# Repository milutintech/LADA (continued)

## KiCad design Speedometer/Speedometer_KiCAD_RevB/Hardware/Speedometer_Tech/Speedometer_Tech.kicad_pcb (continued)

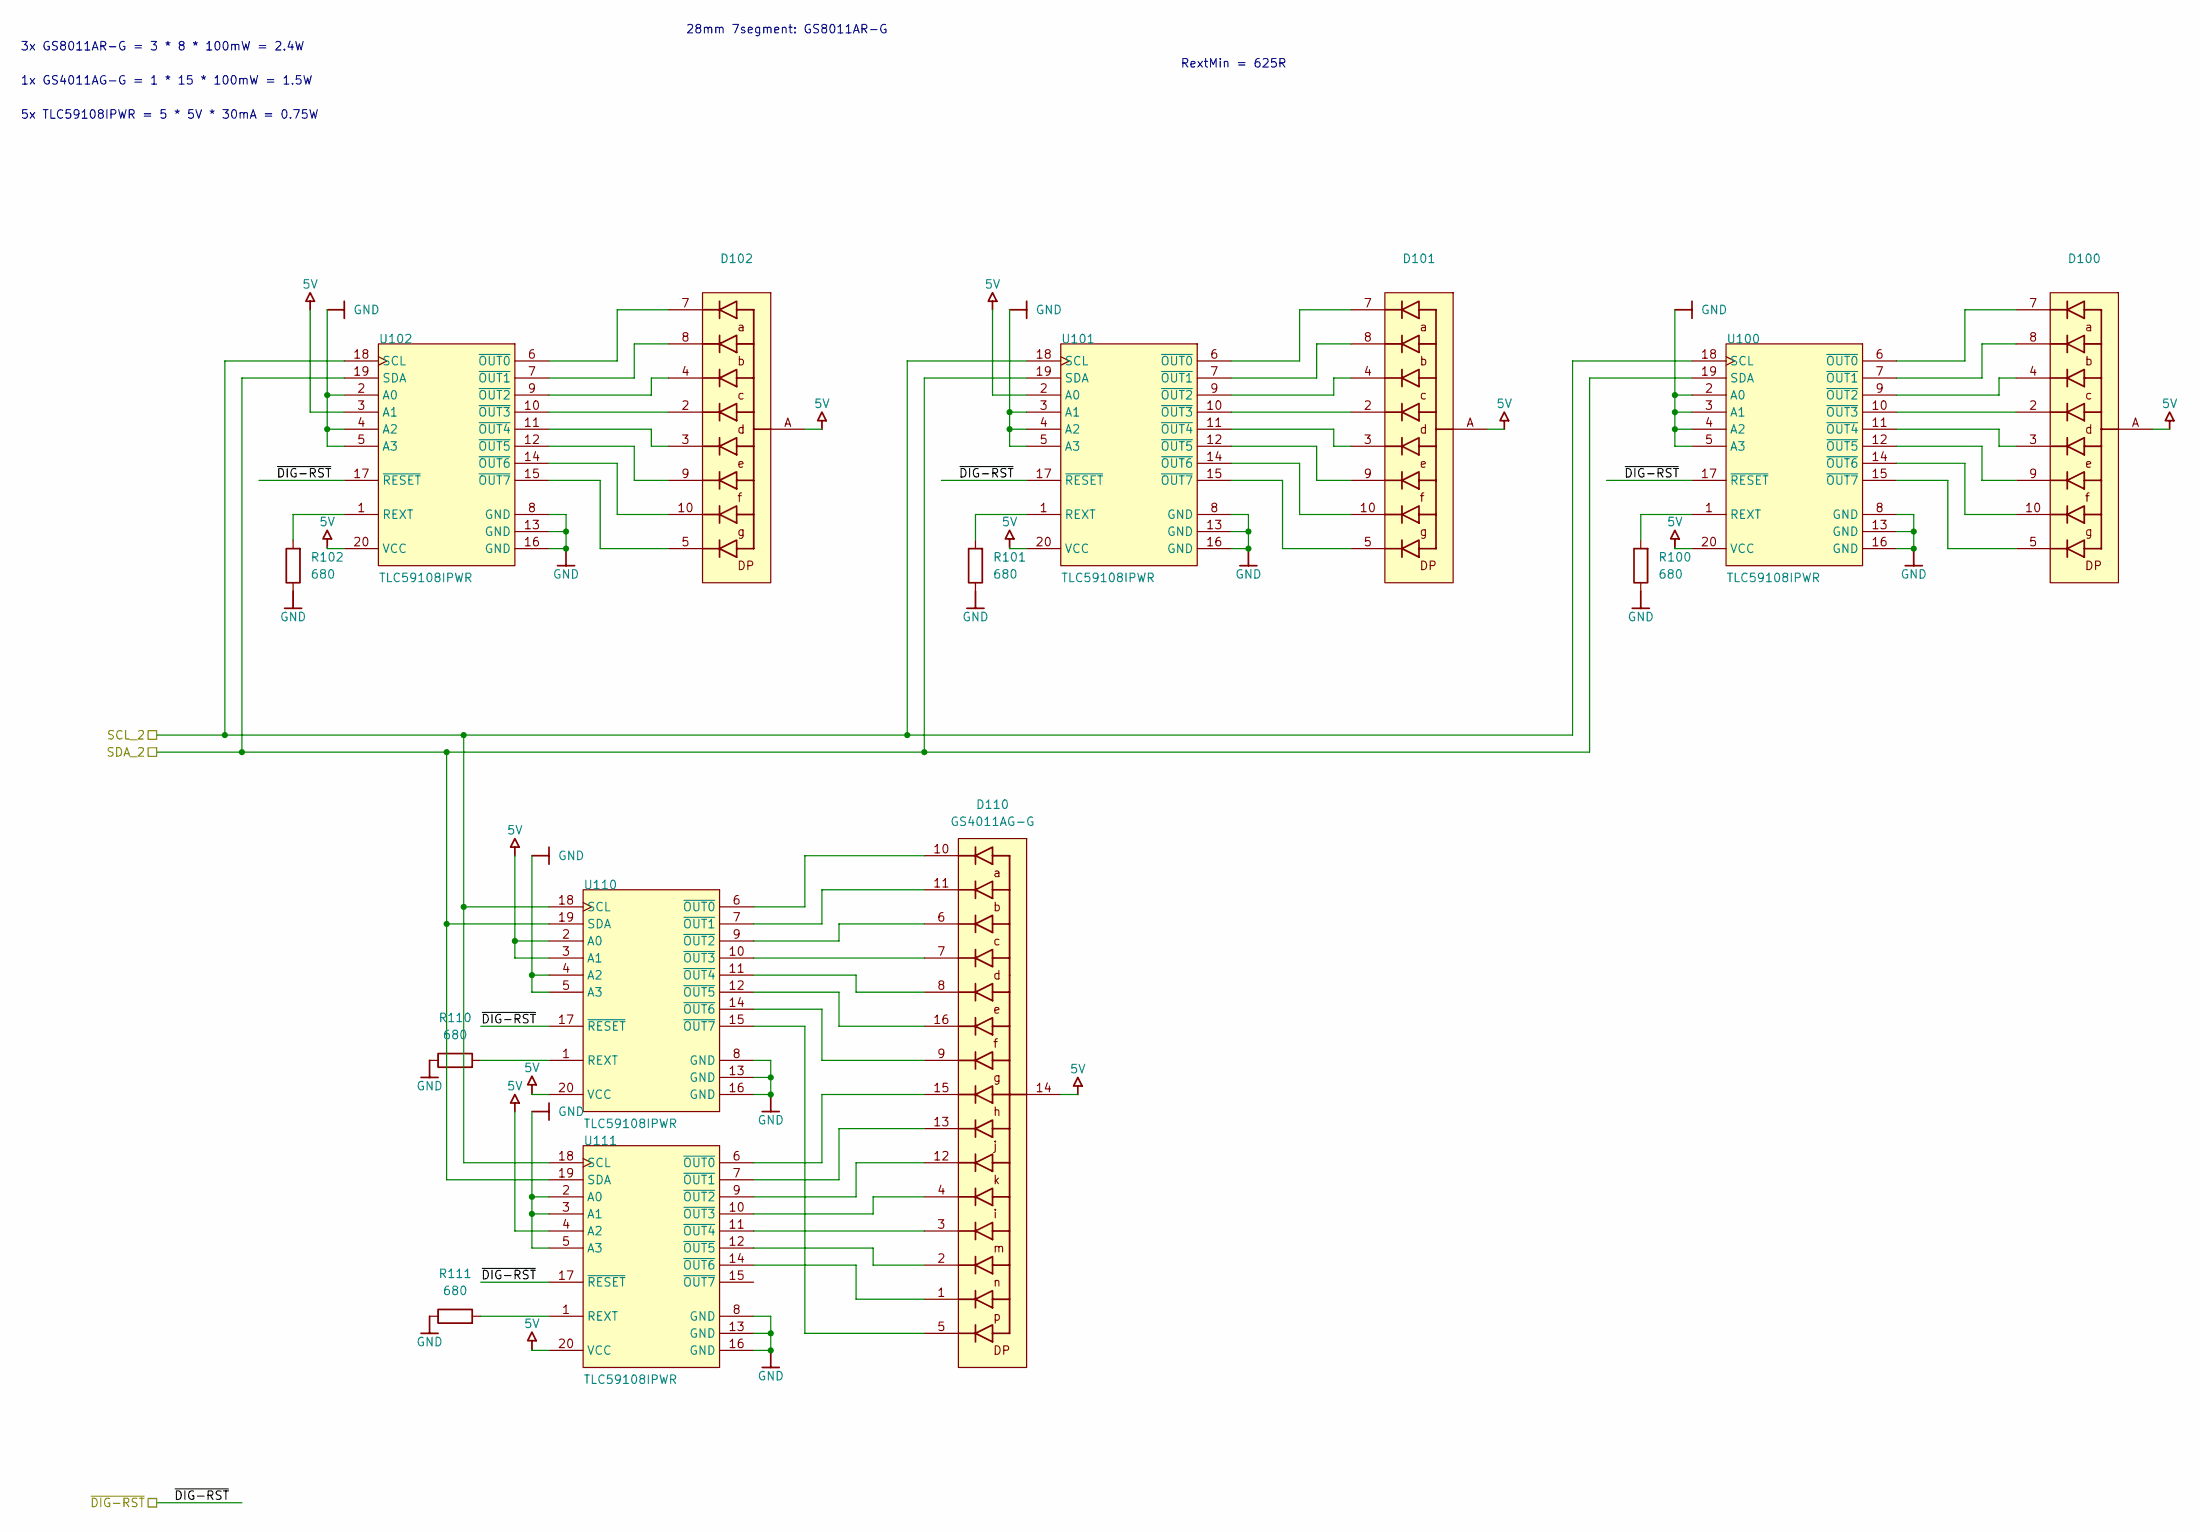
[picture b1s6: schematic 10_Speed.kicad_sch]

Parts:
D100, D101, D102: GS8011AR-G
D110: GS4011AG-G
R100, R101, R102, R110, R111: 680; R_0603_1608Metric
U100, U101, U102, U110, U111: TLC59108IPWR; TSSOP-20_4.4x6.5mm_P0.65mm; PARTNUMBER TLC59108IPWR

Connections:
5V: D100.A, D101.A, D102.A, D110.14, U100.20 (VCC), U101.2 (A0), U101.20 (VCC), U102.3 (A1), U102.20 (VCC), U110.2 (A0), U110.3 (A1), U110.20 (VCC), U111.4 (A2), U111.20 (VCC); also elsewhere on the board
/Distance/~DIG-RST: U100.17 (~RESET), U101.17 (~RESET), U102.17 (~RESET), U110.17 (~RESET), U111.17 (~RESET); also elsewhere on the board
/Speed/SCL_2: U100.18 (SCL), U101.18 (SCL), U102.18 (SCL), U110.18 (SCL), U111.18 (SCL); also elsewhere on the board
/Speed/SDA_2: U100.19 (SDA), U101.19 (SDA), U102.19 (SDA), U110.19 (SDA), U111.19 (SDA); also elsewhere on the board
GND: R100.1, R101.1, R102.1, R110.1, R111.1, U100.2 (A0), U100.3 (A1), U100.4 (A2), U100.5 (A3), U100.8 (GND), U100.13 (GND), U100.16 (GND), U101.3 (A1), U101.4 (A2), U101.5 (A3), U101.8 (GND), U101.13 (GND), U101.16 (GND), U102.2 (A0), U102.4 (A2), U102.5 (A3), U102.8 (GND), U102.13 (GND), U102.16 (GND), U110.4 (A2), U110.5 (A3), U110.8 (GND), U110.13 (GND), U110.16 (GND), U111.2 (A0), U111.3 (A1), U111.5 (A3), U111.8 (GND), U111.13 (GND), U111.16 (GND); also elsewhere on the board
unnamed: R100.2, U100.1 (REXT)
unnamed: D100.7, U100.6 (~OUT0)
unnamed: D100.8, U100.7 (~OUT1)
unnamed: D100.4, U100.9 (~OUT2)
unnamed: D100.2, U100.10 (~OUT3)
unnamed: D100.3, U100.11 (~OUT4)
unnamed: D100.9, U100.12 (~OUT5)
unnamed: D100.10, U100.14 (~OUT6)
unnamed: D100.5, U100.15 (~OUT7)
unnamed: R101.2, U101.1 (REXT)
unnamed: D101.7, U101.6 (~OUT0)
unnamed: D101.8, U101.7 (~OUT1)
unnamed: D101.4, U101.9 (~OUT2)
unnamed: D101.2, U101.10 (~OUT3)
unnamed: D101.3, U101.11 (~OUT4)
unnamed: D101.9, U101.12 (~OUT5)
unnamed: D101.10, U101.14 (~OUT6)
unnamed: D101.5, U101.15 (~OUT7)
unnamed: R102.2, U102.1 (REXT)
unnamed: D102.7, U102.6 (~OUT0)
unnamed: D102.8, U102.7 (~OUT1)
unnamed: D102.4, U102.9 (~OUT2)
unnamed: D102.2, U102.10 (~OUT3)
unnamed: D102.3, U102.11 (~OUT4)
unnamed: D102.9, U102.12 (~OUT5)
unnamed: D102.10, U102.14 (~OUT6)
unnamed: D102.5, U102.15 (~OUT7)
unnamed: R110.2, U110.1 (REXT)
unnamed: D110.10, U110.6 (~OUT0)
unnamed: D110.11, U110.7 (~OUT1)
unnamed: D110.6, U110.9 (~OUT2)
unnamed: D110.7, U110.10 (~OUT3)
unnamed: D110.8, U110.11 (~OUT4)
unnamed: D110.16, U110.12 (~OUT5)
unnamed: D110.9, U110.14 (~OUT6)
unnamed: D110.5, U110.15 (~OUT7)
unnamed: R111.2, U111.1 (REXT)
unnamed: D110.15, U111.6 (~OUT0)
unnamed: D110.13, U111.7 (~OUT1)
unnamed: D110.12, U111.9 (~OUT2)
unnamed: D110.4, U111.10 (~OUT3)
unnamed: D110.3, U111.11 (~OUT4)
unnamed: D110.2, U111.12 (~OUT5)
unnamed: D110.1, U111.14 (~OUT6)

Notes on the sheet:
28mm 7segment: GS8011AR-G
RextMin = 625R
5x TLC59108IPWR = 5 * 5V * 30mA = 0.75W
3x GS8011AR-G = 3 * 8 * 100mW = 2.4W
1x GS4011AG-G = 1 * 15 * 100mW = 1.5W

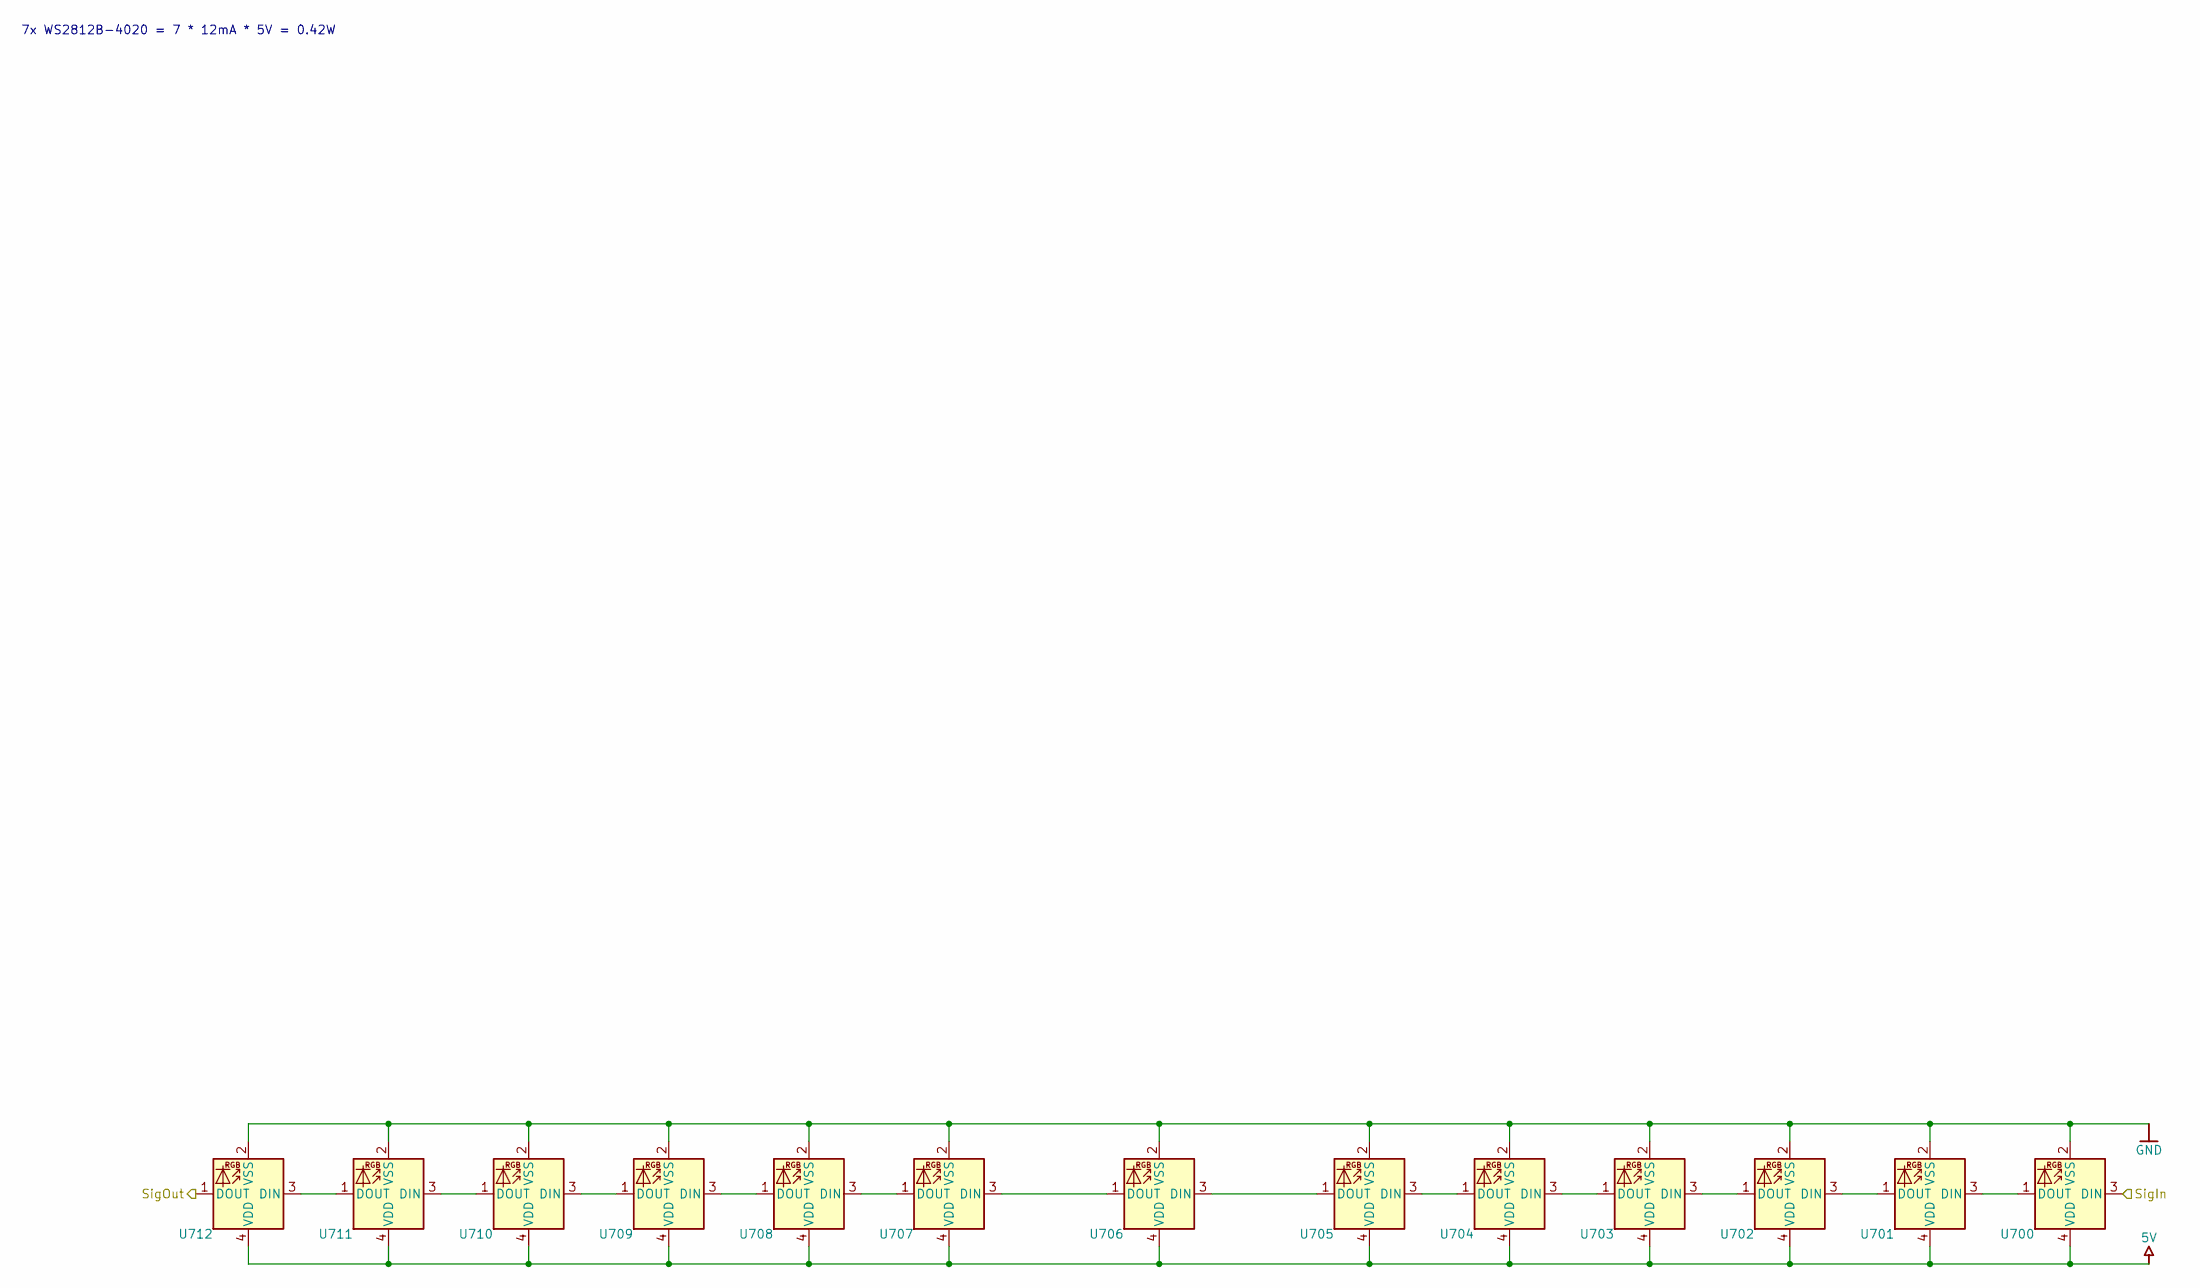
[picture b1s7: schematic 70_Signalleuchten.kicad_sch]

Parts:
U700, U701, U702, U703, U704, U705, U706, U707, U708, U709, U710, U711, U712: WS2812B-4020_2; LED_WS2812B-2020_PLCC4_2.0x2.0mm

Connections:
5V: U700.4 (VDD), U701.4 (VDD), U702.4 (VDD), U703.4 (VDD), U704.4 (VDD), U705.4 (VDD), U706.4 (VDD), U707.4 (VDD), U708.4 (VDD), U709.4 (VDD), U710.4 (VDD), U711.4 (VDD), U712.4 (VDD); also elsewhere on the board
/SOC/SocOut: U700.3 (DIN); also elsewhere on the board
/States/SigOut: U712.1 (DOUT); also elsewhere on the board
GND: U700.2 (VSS), U701.2 (VSS), U702.2 (VSS), U703.2 (VSS), U704.2 (VSS), U705.2 (VSS), U706.2 (VSS), U707.2 (VSS), U708.2 (VSS), U709.2 (VSS), U710.2 (VSS), U711.2 (VSS), U712.2 (VSS); also elsewhere on the board
unnamed: U700.1 (DOUT), U701.3 (DIN)
unnamed: U701.1 (DOUT), U702.3 (DIN)
unnamed: U702.1 (DOUT), U703.3 (DIN)
unnamed: U703.1 (DOUT), U704.3 (DIN)
unnamed: U704.1 (DOUT), U705.3 (DIN)
unnamed: U705.1 (DOUT), U706.3 (DIN)
unnamed: U706.1 (DOUT), U707.3 (DIN)
unnamed: U707.1 (DOUT), U708.3 (DIN)
unnamed: U708.1 (DOUT), U709.3 (DIN)
unnamed: U709.1 (DOUT), U710.3 (DIN)
unnamed: U710.1 (DOUT), U711.3 (DIN)
unnamed: U711.1 (DOUT), U712.3 (DIN)

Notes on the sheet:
7x WS2812B-4020 = 7 * 12mA * 5V = 0.42W

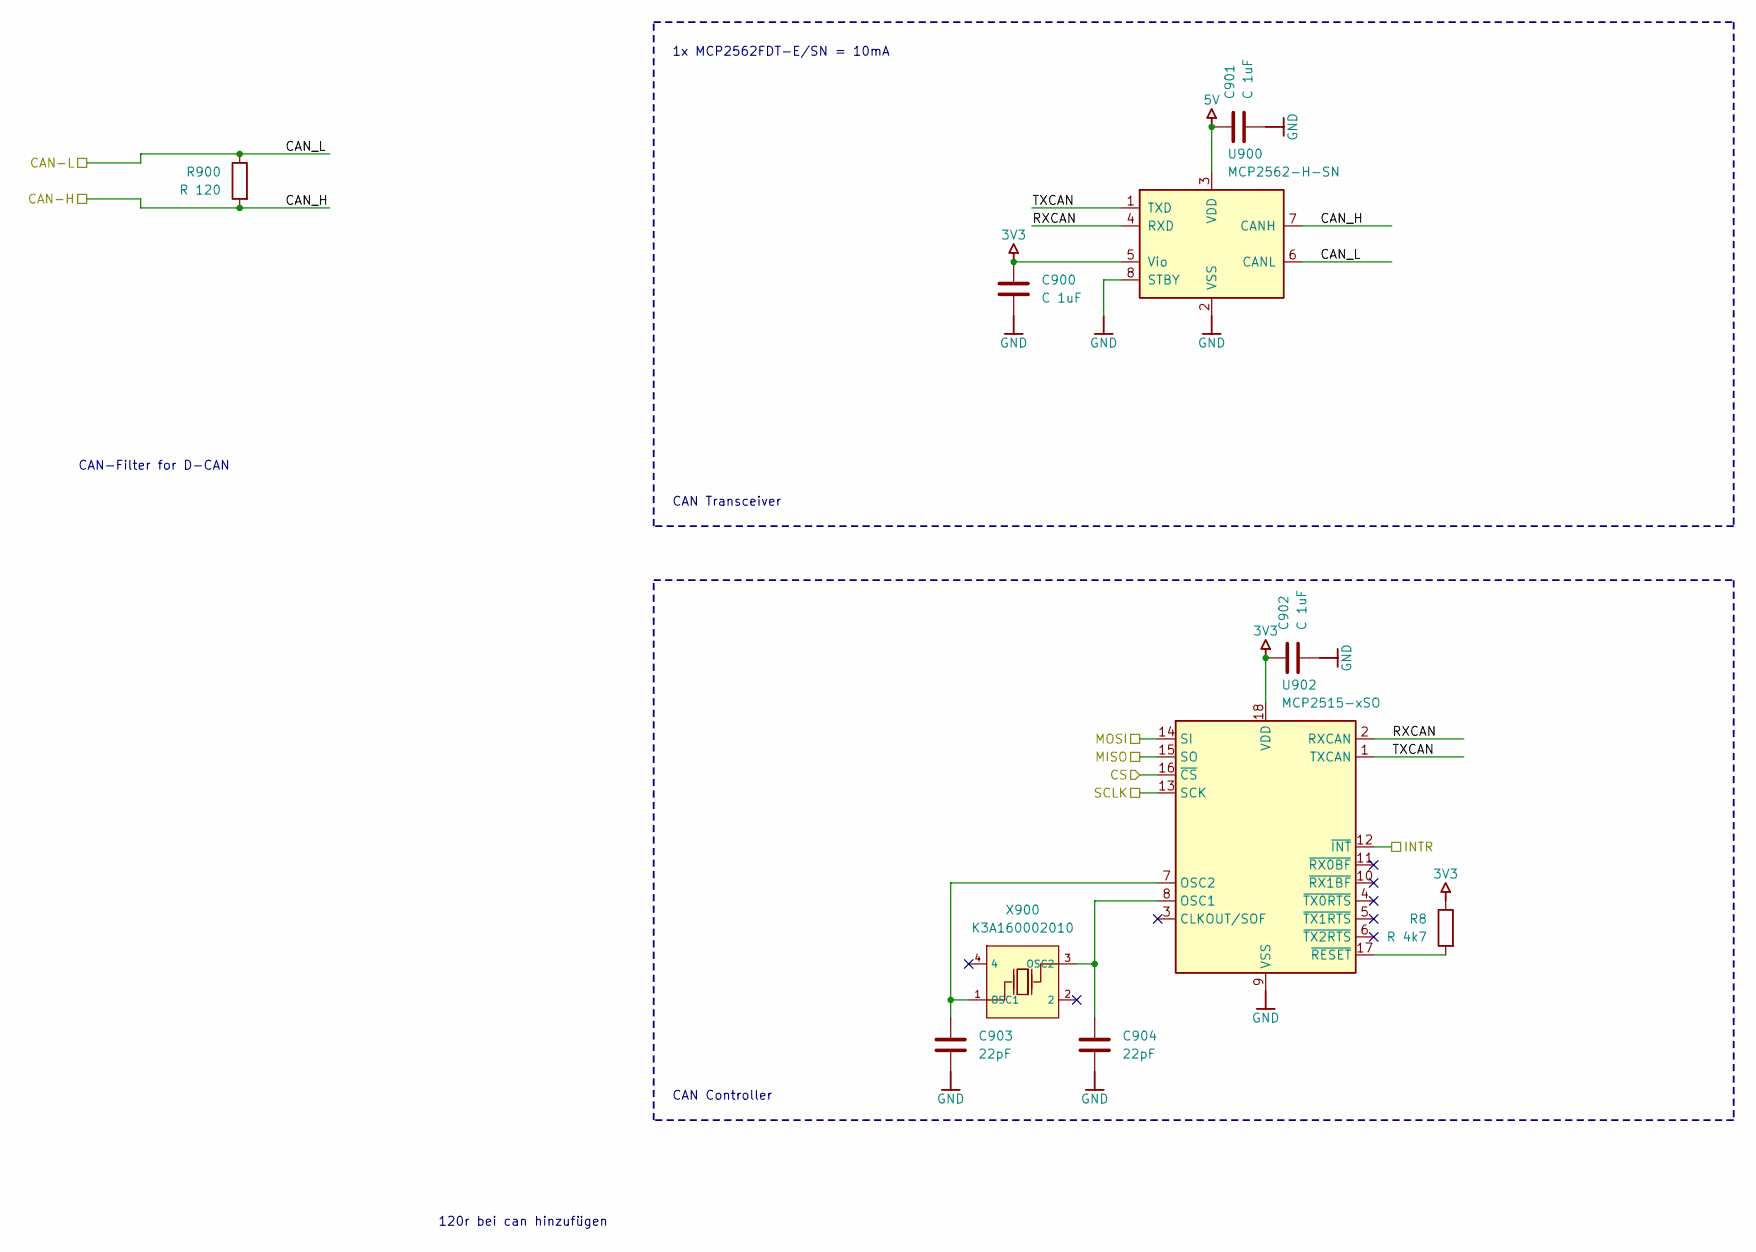
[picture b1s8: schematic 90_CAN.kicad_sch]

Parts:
C900, C901, C902: C 1uF; C_0603_1608Metric
C903, C904: 22pF; C_0603_1608Metric
R8: R 4k7; R_0603_1608Metric
R900: R 120; R_0603_1608Metric
U900: MCP2562-H-SN; SOIC-8_3.9x4.9mm_P1.27mm
U902: MCP2515-xSO; SOIC-18W_7.5x11.6mm_P1.27mm
X900: K3A160002010; Crystal_SMD_3225-4Pin_3.2x2.5mm; LCSC C368736

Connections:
3V3: C900.1, C902.1, R8.1, U900.5 (Vio), U902.18 (VDD); also elsewhere on the board
5V: C901.1, U900.3 (VDD); also elsewhere on the board
/CAN/CAN_H: R900.2, U900.7 (CANH); also elsewhere on the board
/CAN/CAN_L: R900.1, U900.6 (CANL); also elsewhere on the board
/CAN/INTR: U902.12 (~INT); also elsewhere on the board
/CAN/RXCAN: U900.4 (RXD), U902.2 (RXCAN)
/CAN/SCLK: U902.13 (SCK); also elsewhere on the board
/CAN/TXCAN: U900.1 (TXD), U902.1 (TXCAN)
/esp32s3/CS: U902.16 (~CS); also elsewhere on the board
/esp32s3/MISO: U902.15 (SO); also elsewhere on the board
/esp32s3/MOSI: U902.14 (SI); also elsewhere on the board
GND: C900.2, C901.2, C902.2, C903.2, C904.2, U900.2 (VSS), U900.8 (STBY), U902.9 (VSS); also elsewhere on the board
unnamed: C904.1, U902.8 (OSC1), X900.3 (OSC2)
unnamed: C903.1, U902.7 (OSC2), X900.1 (OSC1)
unnamed: R8.2, U902.17 (~RESET)

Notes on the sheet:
CAN-Filter for D-CAN
1x MCP2562FDT-E/SN = 10mA
120r bei can hinzufügen
CAN Transceiver
CAN Controller

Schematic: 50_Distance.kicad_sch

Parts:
D510, D511, D512, D513, D514, D515, D520, D521, D522, D523: 10mm 7-Segment; GS2011AG-G
R510, R511, R512, R513, R514, R515, R520, R521, R522, R523: 680; R_0603_1608Metric
U510, U511, U512, U513, U514, U515, U520, U521, U522, U523: TLC59108IPWR; TSSOP-20_4.4x6.5mm_P0.65mm; PARTNUMBER TLC59108IPWR

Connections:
5V: D510.A, D511.A, D512.A, D513.A, D514.A, D515.A, D520.A, D521.A, D522.A, D523.A, U510.20 (VCC), U511.2 (A0), U511.20 (VCC), U512.3 (A1), U512.20 (VCC), U513.2 (A0), U513.3 (A1), U513.20 (VCC), U514.4 (A2), U514.20 (VCC), U515.2 (A0), U515.4 (A2), U515.20 (VCC), U520.3 (A1), U520.4 (A2), U520.20 (VCC), U521.2 (A0), U521.3 (A1), U521.4 (A2), U521.20 (VCC), U522.5 (A3), U522.20 (VCC), U523.2 (A0), U523.5 (A3), U523.20 (VCC); also elsewhere on the board
/Distance/SCL: U510.18 (SCL), U511.18 (SCL), U512.18 (SCL), U513.18 (SCL), U514.18 (SCL), U515.18 (SCL), U520.18 (SCL), U521.18 (SCL), U522.18 (SCL), U523.18 (SCL); also elsewhere on the board
/Distance/SDA: U510.19 (SDA), U511.19 (SDA), U512.19 (SDA), U513.19 (SDA), U514.19 (SDA), U515.19 (SDA), U520.19 (SDA), U521.19 (SDA), U522.19 (SDA), U523.19 (SDA); also elsewhere on the board
/Distance/~DIG-RST: U510.17 (~RESET), U511.17 (~RESET), U512.17 (~RESET), U513.17 (~RESET), U514.17 (~RESET), U515.17 (~RESET), U520.17 (~RESET), U521.17 (~RESET), U522.17 (~RESET), U523.17 (~RESET); also elsewhere on the board
GND: R510.2, R511.2, R512.2, R513.2, R514.2, R515.2, R520.2, R521.2, R522.2, R523.2, U510.2 (A0), U510.3 (A1), U510.4 (A2), U510.5 (A3), U510.8 (GND), U510.13 (GND), U510.16 (GND), U511.3 (A1), U511.4 (A2), U511.5 (A3), U511.8 (GND), U511.13 (GND), U511.16 (GND), U512.2 (A0), U512.4 (A2), U512.5 (A3), U512.8 (GND), U512.13 (GND), U512.16 (GND), U513.4 (A2), U513.5 (A3), U513.8 (GND), U513.13 (GND), U513.16 (GND), U514.2 (A0), U514.3 (A1), U514.5 (A3), U514.8 (GND), U514.13 (GND), U514.16 (GND), U515.3 (A1), U515.5 (A3), U515.8 (GND), U515.13 (GND), U515.16 (GND), U520.2 (A0), U520.5 (A3), U520.8 (GND), U520.13 (GND), U520.16 (GND), U521.5 (A3), U521.8 (GND), U521.13 (GND), U521.16 (GND), U522.2 (A0), U522.3 (A1), U522.4 (A2), U522.8 (GND), U522.13 (GND), U522.16 (GND), U523.3 (A1), U523.4 (A2), U523.8 (GND), U523.13 (GND), U523.16 (GND); also elsewhere on the board
unnamed: R510.1, U510.1 (REXT)
unnamed: D510.7, U510.6 (~OUT0)
unnamed: D510.6, U510.7 (~OUT1)
unnamed: D510.4, U510.9 (~OUT2)
unnamed: D510.2, U510.10 (~OUT3)
unnamed: D510.1, U510.11 (~OUT4)
unnamed: D510.9, U510.12 (~OUT5)
unnamed: D510.10, U510.14 (~OUT6)
unnamed: D510.5, U510.15 (~OUT7)
unnamed: R511.1, U511.1 (REXT)
unnamed: D511.7, U511.6 (~OUT0)
unnamed: D511.6, U511.7 (~OUT1)
unnamed: D511.4, U511.9 (~OUT2)
unnamed: D511.2, U511.10 (~OUT3)
unnamed: D511.1, U511.11 (~OUT4)
unnamed: D511.9, U511.12 (~OUT5)
unnamed: D511.10, U511.14 (~OUT6)
unnamed: D511.5, U511.15 (~OUT7)
unnamed: R512.1, U512.1 (REXT)
unnamed: D512.7, U512.6 (~OUT0)
unnamed: D512.6, U512.7 (~OUT1)
unnamed: D512.4, U512.9 (~OUT2)
unnamed: D512.2, U512.10 (~OUT3)
unnamed: D512.1, U512.11 (~OUT4)
unnamed: D512.9, U512.12 (~OUT5)
unnamed: D512.10, U512.14 (~OUT6)
unnamed: D512.5, U512.15 (~OUT7)
unnamed: R513.1, U513.1 (REXT)
unnamed: D513.7, U513.6 (~OUT0)
unnamed: D513.6, U513.7 (~OUT1)
unnamed: D513.4, U513.9 (~OUT2)
unnamed: D513.2, U513.10 (~OUT3)
unnamed: D513.1, U513.11 (~OUT4)
unnamed: D513.9, U513.12 (~OUT5)
unnamed: D513.10, U513.14 (~OUT6)
unnamed: D513.5, U513.15 (~OUT7)
unnamed: R514.1, U514.1 (REXT)
unnamed: D514.7, U514.6 (~OUT0)
unnamed: D514.6, U514.7 (~OUT1)
unnamed: D514.4, U514.9 (~OUT2)
unnamed: D514.2, U514.10 (~OUT3)
unnamed: D514.1, U514.11 (~OUT4)
unnamed: D514.9, U514.12 (~OUT5)
unnamed: D514.10, U514.14 (~OUT6)
unnamed: D514.5, U514.15 (~OUT7)
unnamed: R515.1, U515.1 (REXT)
unnamed: D515.7, U515.6 (~OUT0)
unnamed: D515.6, U515.7 (~OUT1)
unnamed: D515.4, U515.9 (~OUT2)
unnamed: D515.2, U515.10 (~OUT3)
unnamed: D515.1, U515.11 (~OUT4)
unnamed: D515.9, U515.12 (~OUT5)
unnamed: D515.10, U515.14 (~OUT6)
unnamed: D515.5, U515.15 (~OUT7)
unnamed: R520.1, U520.1 (REXT)
unnamed: D520.7, U520.6 (~OUT0)
unnamed: D520.6, U520.7 (~OUT1)
unnamed: D520.4, U520.9 (~OUT2)
unnamed: D520.2, U520.10 (~OUT3)
unnamed: D520.1, U520.11 (~OUT4)
unnamed: D520.9, U520.12 (~OUT5)
unnamed: D520.10, U520.14 (~OUT6)
unnamed: D520.5, U520.15 (~OUT7)
unnamed: R521.1, U521.1 (REXT)
unnamed: D521.7, U521.6 (~OUT0)
unnamed: D521.6, U521.7 (~OUT1)
unnamed: D521.4, U521.9 (~OUT2)
unnamed: D521.2, U521.10 (~OUT3)
unnamed: D521.1, U521.11 (~OUT4)
unnamed: D521.9, U521.12 (~OUT5)
unnamed: D521.10, U521.14 (~OUT6)
unnamed: D521.5, U521.15 (~OUT7)
unnamed: R522.1, U522.1 (REXT)
unnamed: D522.7, U522.6 (~OUT0)
unnamed: D522.6, U522.7 (~OUT1)
unnamed: D522.4, U522.9 (~OUT2)
unnamed: D522.2, U522.10 (~OUT3)
unnamed: D522.1, U522.11 (~OUT4)
unnamed: D522.9, U522.12 (~OUT5)
unnamed: D522.10, U522.14 (~OUT6)
unnamed: D522.5, U522.15 (~OUT7)
unnamed: R523.1, U523.1 (REXT)
unnamed: D523.7, U523.6 (~OUT0)
unnamed: D523.6, U523.7 (~OUT1)
unnamed: D523.4, U523.9 (~OUT2)
unnamed: D523.2, U523.10 (~OUT3)
unnamed: D523.1, U523.11 (~OUT4)
unnamed: D523.9, U523.12 (~OUT5)
unnamed: D523.10, U523.14 (~OUT6)
unnamed: D523.5, U523.15 (~OUT7)

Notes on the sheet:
Numbering from right to left
Trip km
10x GS2011AG-G = 10 * 8 * 100mW = 8W
Total km
10x TLC59108IPWR = 10 * 5V * 30mA = 1.5W

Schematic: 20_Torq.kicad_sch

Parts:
U205, U206, U207, U208, U209, U210, U211, U212, U213, U214, U215, U216, U217, U218, U219, U220, U221, U222, U223, U224, U225, U226, U227, U228, U229, U230, U231, U232, U233, U234, U235, U236, U237, U238, U239, U240, U241: WS2812B-4020_2; LED_WS2812B-2020_PLCC4_2.0x2.0mm

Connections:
5V: U205.4 (VDD), U206.4 (VDD), U207.4 (VDD), U208.4 (VDD), U209.4 (VDD), U210.4 (VDD), U211.4 (VDD), U212.4 (VDD), U213.4 (VDD), U214.4 (VDD), U215.4 (VDD), U216.4 (VDD), U217.4 (VDD), U218.4 (VDD), U219.4 (VDD), U220.4 (VDD), U221.4 (VDD), U222.4 (VDD), U223.4 (VDD), U224.4 (VDD), U225.4 (VDD), U226.4 (VDD), U227.4 (VDD), U228.4 (VDD), U229.4 (VDD), U230.4 (VDD), U231.4 (VDD), U232.4 (VDD), U233.4 (VDD), U234.4 (VDD), U235.4 (VDD), U236.4 (VDD), U237.4 (VDD), U238.4 (VDD), U239.4 (VDD), U240.4 (VDD), U241.4 (VDD); also elsewhere on the board
/SOC/SocIn: U241.1 (DOUT); also elsewhere on the board
/Torq/TorqIn: U205.3 (DIN); also elsewhere on the board
GND: U205.2 (VSS), U206.2 (VSS), U207.2 (VSS), U208.2 (VSS), U209.2 (VSS), U210.2 (VSS), U211.2 (VSS), U212.2 (VSS), U213.2 (VSS), U214.2 (VSS), U215.2 (VSS), U216.2 (VSS), U217.2 (VSS), U218.2 (VSS), U219.2 (VSS), U220.2 (VSS), U221.2 (VSS), U222.2 (VSS), U223.2 (VSS), U224.2 (VSS), U225.2 (VSS), U226.2 (VSS), U227.2 (VSS), U228.2 (VSS), U229.2 (VSS), U230.2 (VSS), U231.2 (VSS), U232.2 (VSS), U233.2 (VSS), U234.2 (VSS), U235.2 (VSS), U236.2 (VSS), U237.2 (VSS), U238.2 (VSS), U239.2 (VSS), U240.2 (VSS), U241.2 (VSS); also elsewhere on the board
unnamed: U205.1 (DOUT), U206.3 (DIN)
unnamed: U206.1 (DOUT), U207.3 (DIN)
unnamed: U207.1 (DOUT), U208.3 (DIN)
unnamed: U208.1 (DOUT), U209.3 (DIN)
unnamed: U209.1 (DOUT), U210.3 (DIN)
unnamed: U210.1 (DOUT), U211.3 (DIN)
unnamed: U211.1 (DOUT), U212.3 (DIN)
unnamed: U212.1 (DOUT), U213.3 (DIN)
unnamed: U213.1 (DOUT), U214.3 (DIN)
unnamed: U214.1 (DOUT), U215.3 (DIN)
unnamed: U215.1 (DOUT), U216.3 (DIN)
unnamed: U216.1 (DOUT), U217.3 (DIN)
unnamed: U217.1 (DOUT), U218.3 (DIN)
unnamed: U218.1 (DOUT), U219.3 (DIN)
unnamed: U219.1 (DOUT), U220.3 (DIN)
unnamed: U220.1 (DOUT), U221.3 (DIN)
unnamed: U221.1 (DOUT), U222.3 (DIN)
unnamed: U222.1 (DOUT), U223.3 (DIN)
unnamed: U223.1 (DOUT), U224.3 (DIN)
unnamed: U224.1 (DOUT), U225.3 (DIN)
unnamed: U225.1 (DOUT), U226.3 (DIN)
unnamed: U226.1 (DOUT), U227.3 (DIN)
unnamed: U227.1 (DOUT), U228.3 (DIN)
unnamed: U228.1 (DOUT), U229.3 (DIN)
unnamed: U229.1 (DOUT), U230.3 (DIN)
unnamed: U230.1 (DOUT), U231.3 (DIN)
unnamed: U231.1 (DOUT), U232.3 (DIN)
unnamed: U232.1 (DOUT), U233.3 (DIN)
unnamed: U233.1 (DOUT), U234.3 (DIN)
unnamed: U234.1 (DOUT), U235.3 (DIN)
unnamed: U235.1 (DOUT), U236.3 (DIN)
unnamed: U236.1 (DOUT), U237.3 (DIN)
unnamed: U237.1 (DOUT), U238.3 (DIN)
unnamed: U238.1 (DOUT), U239.3 (DIN)
unnamed: U239.1 (DOUT), U240.3 (DIN)
unnamed: U240.1 (DOUT), U241.3 (DIN)

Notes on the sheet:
20x WS2812B-4020 = 20 * 12mA * 5V = 1.2W

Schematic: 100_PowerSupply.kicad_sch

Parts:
C1001, C1002, C1011, C1012: 10uF; C_0805_2012Metric
C1003, C1013: 100nF; C_0805_2012Metric
C1004, C1005, C1006, C1014, C1015, C1016: 22uF; C_0805_2012Metric
L1001: SRN8040-2R2Y; L_Bourns-SRN8040_8x8.15mm
L1011: SRN8040-3R3Y; L_Bourns-SRN8040_8x8.15mm
R1001: 33.2k; R_0603_1608Metric
R1002, R1012: 10k; R_0603_1608Metric
R1011: 56.2k; R_0603_1608Metric
U1001, U1011: TPS563200; SOT-23-6

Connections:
3V3: C1004.1, C1005.1, C1006.1, L1001.2, R1001.1; also elsewhere on the board
5V: C1014.1, C1015.1, C1016.1, L1011.2, R1011.1; also elsewhere on the board
/DC-DC/3V3_DCDC_Switch: C1003.1, L1001.1, U1001.2 (SW)
/DC-DC/5V_DCDC_Switch: C1013.1, L1011.1, U1011.2 (SW)
GND: C1001.2, C1002.2, C1004.2, C1005.2, C1006.2, C1011.2, C1012.2, C1014.2, C1015.2, C1016.2, R1002.2, R1012.2, U1001.1 (GND), U1011.1 (GND); also elsewhere on the board
KL30i: C1001.1, C1002.1, C1011.1, C1012.1, U1001.3 (VIN), U1001.5 (EN), U1011.3 (VIN), U1011.5 (EN); also elsewhere on the board
unnamed: C1003.2, U1001.6 (VBST)
unnamed: R1001.2, R1002.1, U1001.4 (VFB)
unnamed: C1013.2, U1011.6 (VBST)
unnamed: R1011.2, R1012.1, U1011.4 (VFB)

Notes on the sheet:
TI-WeBench 3V3@2A
3V3: 0.8-1A
5V: 1.3-1.5A
TI-WeBench 5V@2A

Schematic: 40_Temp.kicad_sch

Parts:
U401, U402, U403, U404, U405, U406, U407, U408, U409, U410, U411, U412, U413, U414, U415, U416, U417, U418, U419, U420, U421, U422, U423, U424, U425, U426: WS2812B-4020_2; LED_WS2812B-2020_PLCC4_2.0x2.0mm

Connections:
5V: U401.4 (VDD), U402.4 (VDD), U403.4 (VDD), U404.4 (VDD), U405.4 (VDD), U406.4 (VDD), U407.4 (VDD), U408.4 (VDD), U409.4 (VDD), U410.4 (VDD), U411.4 (VDD), U412.4 (VDD), U413.4 (VDD), U414.4 (VDD), U415.4 (VDD), U416.4 (VDD), U417.4 (VDD), U418.4 (VDD), U419.4 (VDD), U420.4 (VDD), U421.4 (VDD), U422.4 (VDD), U423.4 (VDD), U424.4 (VDD), U425.4 (VDD), U426.4 (VDD); also elsewhere on the board
/States/SigOut: U401.3 (DIN); also elsewhere on the board
/Temp/TempOut: U426.1 (DOUT); also elsewhere on the board
GND: U401.2 (VSS), U402.2 (VSS), U403.2 (VSS), U404.2 (VSS), U405.2 (VSS), U406.2 (VSS), U407.2 (VSS), U408.2 (VSS), U409.2 (VSS), U410.2 (VSS), U411.2 (VSS), U412.2 (VSS), U413.2 (VSS), U414.2 (VSS), U415.2 (VSS), U416.2 (VSS), U417.2 (VSS), U418.2 (VSS), U419.2 (VSS), U420.2 (VSS), U421.2 (VSS), U422.2 (VSS), U423.2 (VSS), U424.2 (VSS), U425.2 (VSS), U426.2 (VSS); also elsewhere on the board
unnamed: U401.1 (DOUT), U402.3 (DIN)
unnamed: U402.1 (DOUT), U403.3 (DIN)
unnamed: U403.1 (DOUT), U404.3 (DIN)
unnamed: U404.1 (DOUT), U405.3 (DIN)
unnamed: U405.1 (DOUT), U406.3 (DIN)
unnamed: U406.1 (DOUT), U407.3 (DIN)
unnamed: U407.1 (DOUT), U408.3 (DIN)
unnamed: U408.1 (DOUT), U409.3 (DIN)
unnamed: U409.1 (DOUT), U410.3 (DIN)
unnamed: U410.1 (DOUT), U411.3 (DIN)
unnamed: U411.1 (DOUT), U412.3 (DIN)
unnamed: U412.1 (DOUT), U413.3 (DIN)
unnamed: U413.1 (DOUT), U414.3 (DIN)
unnamed: U414.1 (DOUT), U415.3 (DIN)
unnamed: U415.1 (DOUT), U416.3 (DIN)
unnamed: U416.1 (DOUT), U417.3 (DIN)
unnamed: U417.1 (DOUT), U418.3 (DIN)
unnamed: U418.1 (DOUT), U419.3 (DIN)
unnamed: U419.1 (DOUT), U420.3 (DIN)
unnamed: U420.1 (DOUT), U421.3 (DIN)
unnamed: U421.1 (DOUT), U422.3 (DIN)
unnamed: U422.1 (DOUT), U423.3 (DIN)
unnamed: U423.1 (DOUT), U424.3 (DIN)
unnamed: U424.1 (DOUT), U425.3 (DIN)
unnamed: U425.1 (DOUT), U426.3 (DIN)

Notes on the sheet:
18x WS2812B-4020 = 18 * 12mA * 5V = 1.08W
110
Kühlwasser Symbol

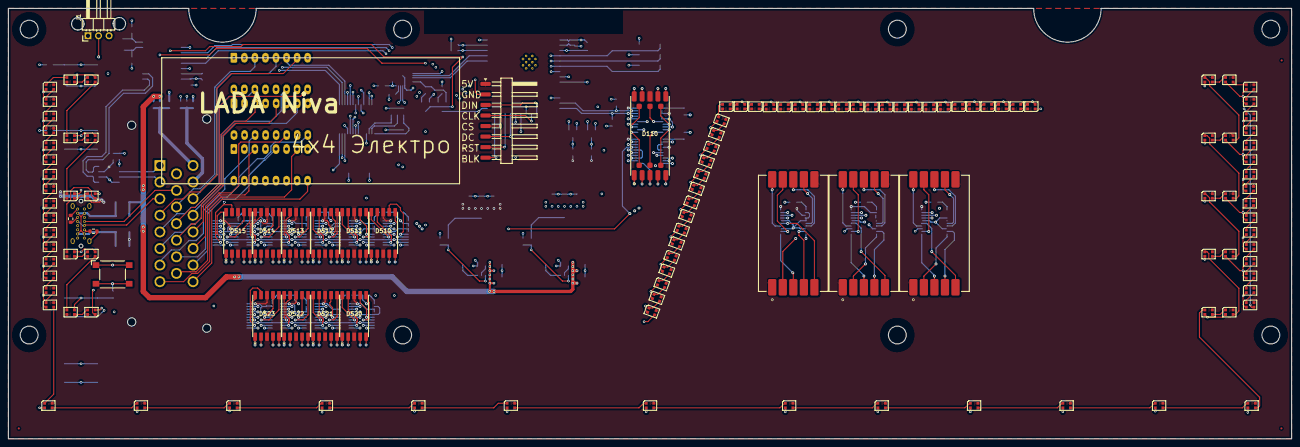
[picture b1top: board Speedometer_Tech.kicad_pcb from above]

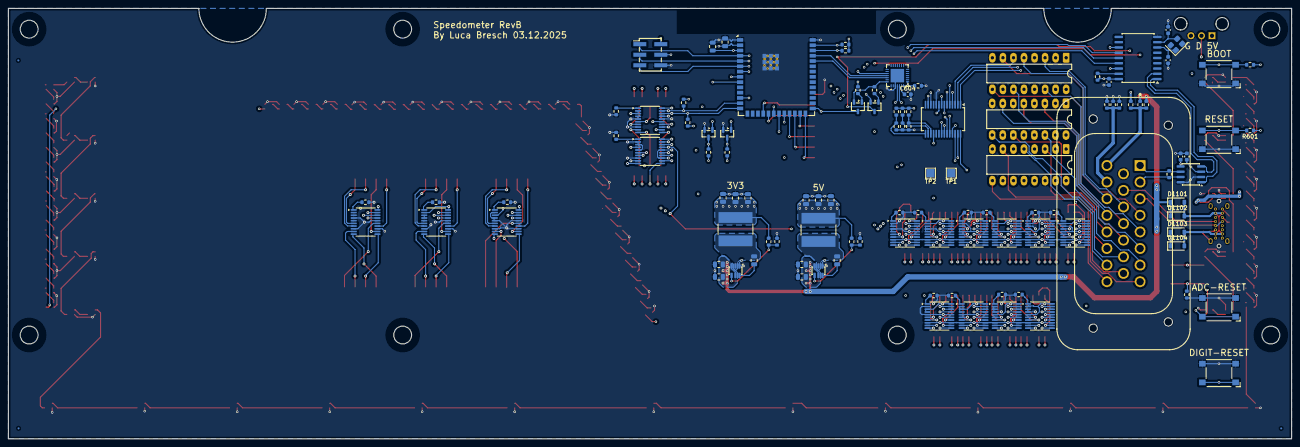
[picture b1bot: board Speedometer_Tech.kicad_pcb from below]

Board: 4 copper layers, 309.2 x 103.7 mm, 246 parts (114 on the bottom side), 329 nets.

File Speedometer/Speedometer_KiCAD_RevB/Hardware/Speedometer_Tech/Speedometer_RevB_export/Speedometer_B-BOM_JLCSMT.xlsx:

Comment | Designator | Footprint | JLCPCB Part #（optional）
WS2812B-4020_2 | U239,U226,U227,U315,U224,U420,U305,U401,U415,U303,U205,U317,U306,U709,U223,U404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 | LED_WS2812B-2020_PLCC4_2.0x2.0mm
10mm 7-Segment | D521,D520,D523,D510,D512,D511,D513,D522,D514,D515 | GS2011AG-G
Conn_01x03_Pin | J1 | PinHeader_1x03_P2.54mm_Horizontal
~ | D101,D102,D100 | GS8011AR-G
GS4011AG-G | D110 | GS4011AG-G
5.1k | R607,R608 | R_0603_1608Metric
SW_Omron_B3FS | S600,S606,S2,S602,S601 | SW_SPST_Omron_B3FS-100xP
YTC-TC16S-24 | U605 | TYPEC-300D-BCP16H100
100nF | C1013,C1003 | C_0805_2012Metric
TLC59108IPWR | U523,U111,U521,U513,U511,U522,U512,U102,U520,U100,U514,U110,U510,U515,U101 | TSSOP-20_4.4x6.5mm_P0.65mm
0R | R18,R16,R17,R14,R15 | R_0603_1608Metric
1uF | C601 | C_0805_2012Metric
2.2k | R603,R602,R612,R611 | R_0603_1608Metric
680 | R521,R523,R110,R514,R522,R510,R101,R515,R513,R100,R512,R511,R520,R111,R102 | R_0603_1608Metric
22pF | C904,C903 | C_0603_1608Metric
R 4k7 | R8 | R_0603_1608Metric
10uF | C1012,C1002,C1001,C1011 | C_0805_2012Metric
33.2k | R1001 | R_0603_1608Metric
56.2k | R1011 | R_0603_1608Metric
0 | R002,R003,R000,R001 | R_0603_1608Metric
22uF | C1016,C1014,C1015,C1006,C1004,C602,C1005 | C_0805_2012Metric
10k | R601,R1002,R605,R606,R1012,R604 | R_0603_1608Metric
776228-1 | J800 | TE_776228-1
2x3 | H602 | PinHeader_2x03_P2.54mm_Vertical_SMD
TPS563200 | U1011,U1001 | SOT-23-6
SBR80520LT1G | D1102,D1104,D1103,D1101 | D_SOD-123
4010 | U3,U4,U5 | DIP-16_W7.62mm_LongPads
BC817 | U602,U604 | SOT-23-3
MCP2562-H-SN | U900 | SOIC-8_3.9x4.9mm_P1.27mm
TestPoint_Probe | TP1,TP2 | TestPoint_Pad_2.0x2.0mm
SRN8040-3R3Y | L1011 | L_Bourns-SRN8040_8x8.15mm
MCP23017_SS | U1 | SSOP-28_5.3x10.2mm_P0.65mm
MCP2515-xSO | U902 | SOIC-18W_7.5x11.6mm_P1.27mm
C 1uF | C900,C902,C901 | C_0603_1608Metric
ESP32-S3-WROOM-1(N8R2) | U601 | ESP32-S3-WROOM-2
R 1k | R609,R610 | R_0603_1608Metric
K3A160002010 | X900 | Crystal_SMD_3225-4Pin_3.2x2.5mm
100nF | C604 | C_0603_1608Metric
1k | R9 | R_0603_1608Metric
100nF | C605 | R_0603_1608Metric
SRN8040-2R2Y | L1001 | L_Bourns-SRN8040_8x8.15mm
100nF | C603 | C_0201_0603Metric
DTC123J | Q601,Q602 | SOT-23
CP2102N-A02-GQFN28R | U603 | VQFN-28-1EP_5x5mm_P0.5mm_EP3.25x3.25mm
R 120 | R900 | R_0603_1608Metric

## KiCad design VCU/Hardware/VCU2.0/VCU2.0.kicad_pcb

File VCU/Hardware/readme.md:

# LADA
> CAN_BUS
> 
> 4x 12V Input RTC Interrupt Capable
> 
> 8x Relays
> 
> 12V Supply
> 
> ADAC Chip
>
> 5V / 3.3V buckwandler

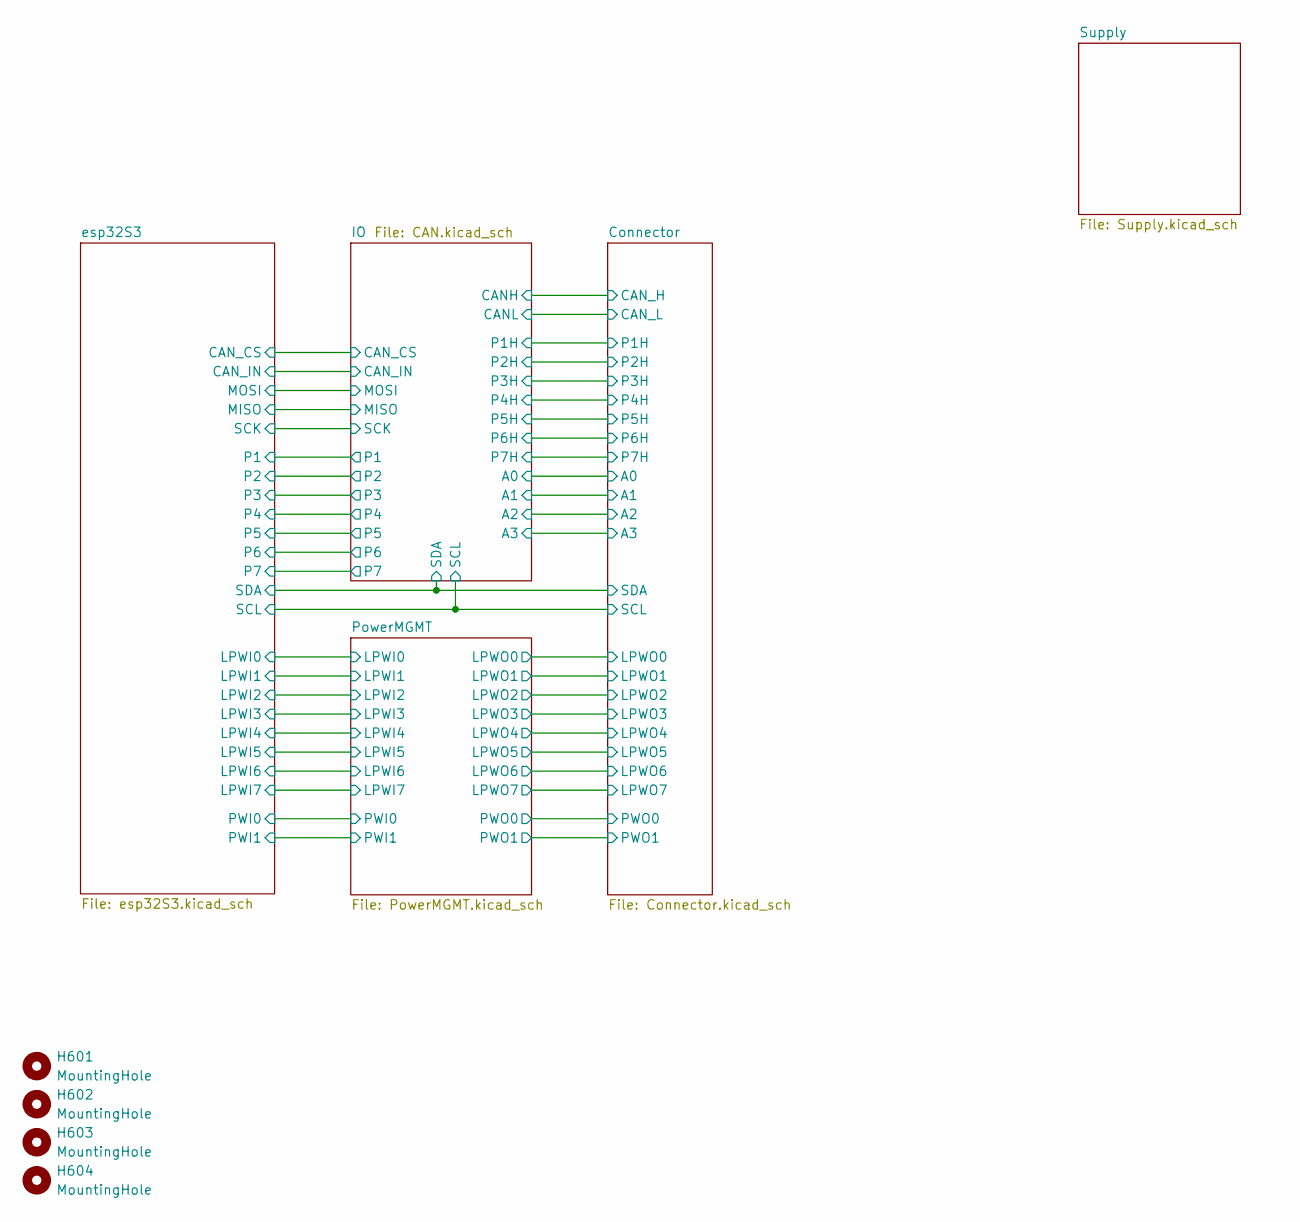
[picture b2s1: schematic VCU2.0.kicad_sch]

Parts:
H601, H602, H603, H604: MountingHole; MountingHole_3.2mm_M3_DIN965
